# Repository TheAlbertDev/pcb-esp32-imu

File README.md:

# ESP32 + IMU PCB

PCB for the Surgery Robotics Project of the Robotics Course of the Biomedical Engineering Degree of the Universitat de Barcelona.

## License

ESP32 + IMU PCB © 2021 by Albert Álvarez-Carulla is licensed under [Attribution-NonCommercial-NoDerivatives 4.0 International.](LICENSE.md)

You can use the [GitHub's citation feature](https://github.blog/2021-08-19-enhanced-support-citations-github/) to cite this work.

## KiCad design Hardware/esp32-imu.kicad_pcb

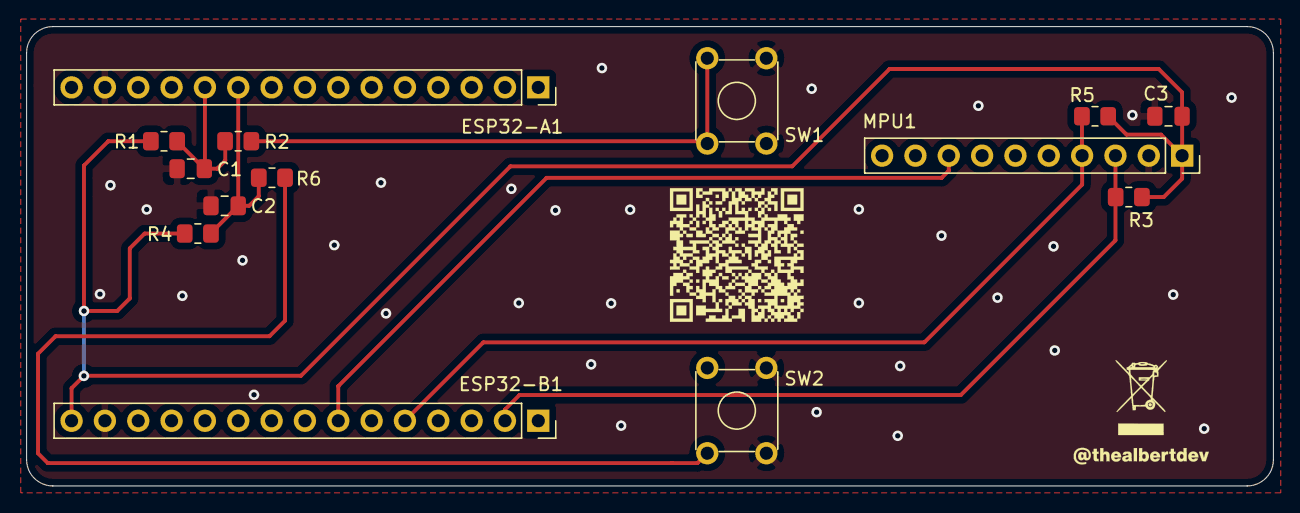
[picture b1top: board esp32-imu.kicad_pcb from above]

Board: 2 copper layers, 95.0 x 35.0 mm, 14 parts (0 on the bottom side), 9 nets.

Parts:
C1, C2, C3: 100n; C_0805_2012Metric_Pad1.18x1.45mm_HandSolder
ESP32-A1, ESP32-B1: Conn_01x15_Female; PinSocket_1x15_P2.54mm_Vertical
MPU1: Conn_01x10_Female; PinSocket_1x10_P2.54mm_Vertical
R1, R4: 10k; R_0805_2012Metric_Pad1.20x1.40mm_HandSolder
R2, R6: 1k; R_0805_2012Metric_Pad1.20x1.40mm_HandSolder
R3, R5: 2k2; R_0805_2012Metric_Pad1.20x1.40mm_HandSolder
SW1, SW2: SW_MEC_5E; SW_TH_Tactile_Omron_B3F-10xx

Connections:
+3V3: C3.1, ESP32-B1.15, MPU1.1, R1.1, R3.1, R4.1, R5.1
/INT: ESP32-B1.7, MPU1.8
/SCL: ESP32-B1.2, MPU1.3, R3.2
/SDA: ESP32-B1.5, MPU1.4, R5.2
GND: C1.2, C2.2, C3.2, ESP32-A1.14, ESP32-B1.14, MPU1.2, SW1.3, SW1.4, SW2.3, SW2.4
unnamed: C1.1, ESP32-A1.11, R1.2, R2.2
unnamed: C2.1, ESP32-A1.10, R4.2, R6.2
unnamed: R2.1, SW1.1, SW1.2
unnamed: R6.1, SW2.1

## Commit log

2021-10-04 First prototype for the workshop
2021-10-12 Version with SMDs for externa external manufacturing
